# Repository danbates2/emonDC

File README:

emonDC
Project status: in production. expected release May 2018.

Measurement of direct current (DC).
This is a project description but also a collection of ideas and findings. All thoughts welcome.
The diversity of approaches could be illustrated by these two websites:
https://www.coolcomponents.co.uk/attopilot-voltage-and-current-sense-breakout-180a.html
http://www.victronenergy.com/upload/documents/Datasheet-Battery-monitoring-EN.pdf
My approach won’t be the only way but you’ll get an idea as you read on. Hopefully it makes sense. I welcome any and all feedback and hope for this to be as complete a project in theory before I begin schematic and PCB designs. Hey, I might even be close to making a decision by now… Also, this isn’t intended to claim ownership of the idea, if anyone wants to pick up the pieces and go for it they’re welcome.

emonDC Project
This unit will be a dual  shunt-monitoring device with wireless Tx capabilities. The device will be powered from the DC voltage source it is measuring, or from batteries. Because of potential outdoor applications the form will make possible the use of Waterproof I.P. rated boxes. A metal case matching emonTX style needs looking at also. The unit design will aim primarily at domestic DC applications, for example, solar photovoltaic and wind generation systems with either grid-tie inverters or battery systems.
Safety needs consideration in different ways. Firstly, short circuit protection needs to exist at different levels of the hardware design to avoid inadvertent damage to the unit, by mal-assembly on part of the manufacturer (PCB) or user (installation). This can be achieved with adding particular components, such as fuses and backup series resistors, in the event of a short. The layout of the components will factor in safety also.
Secondly, protection of connected devices and users from floating ground voltages in certain applications. This can be achieved with a bright yellow warning label stating ‘disconnect DC system before attaching USB/FTDI’ or ‘check for common ground between this unit and devices to be connected before making connection’ or something similar, pending advice.
Hall-effect DC monitoring ICs are simple and provide a degree of electrical isolation, however, they are inflexible and costly. Shunt monitoring provides much greater flexibility, accuracy and cost-effectiveness.

1. The range of requirements in DC monitoring applications require a flexible approach because of…
a. Unidirectional and bidirectional requirements.
b. Amperage Ranges and associated cable cross sectional areas (CSA). For example, household 100A cables are 25mm2 or 16mm2, whereas wire for headers and breadboard carrying up to about 5A are about 0.9mm2. The target measurement range has significant physical design implications. 
c. Different cable/wire CSAs require terminations suitable to their size and application (screw terminals, bolted bus bars, soldered connections, etc.) there is no single solution.
d. Whole battery systems can be monitored with one shunt or individual cells of the system can require a multi-cell monitoring unit.
e. There are also high humidity, marine and automotive applications.

2. If we consider cable sizes and the range of amperages in terms of a suitable termination, the issues make it difficult to see any one PCB realistically and cost-effectively meeting all requirements.
This possibly leads to the solution of designing several different systems according to the requirements. First suggestions might look like:
emonDC50 – Bidirectional DC monitor with integrated yet replaceable / bypassable shunt, accepting up to 6mm2 cable up to 50A, but with customizable sensitivity down for micro amps.
emonDC500 – Unidirectional shunt monitor with external shunt rated up to 500A.
emonDC500duo – Two unidirectional shunt monitors in parallel for measuring two external shunts rated up to 500A, for battery/generator applications.

3. Another option might be to have a two-part system where Tx functions are separated from shunt monitoring functions in two separate PCBs, connected via RJ11 or ribbon cable. This could lend itself to multi-source monitoring effectively. Several different model of the DC monitoring PCB could be developed for a range of applications. Also, the standalone Tx PCB may lend itself to other emon projects in the future.

4. Given the nature of solar, wind and various DC applications there a requirement for a protected, regulated supply. Protected from over voltage. Regulated, smoothed output for powering the shunt monitor, Arduino and RF chip.

5. Failsafe monitoring... Fuses between the shunt and monitor to protect from short circuit conditions.

6. High-side vs. low-side sensing… This shunt monitor needs to be capable of handling both applications, which means using a shunt monitor IC capable of high-side measurement. The device should ideally handle a large common-mode voltage, say up to 80V, and protection be in place for voltage over the common-mode voltage limit of the chip.

Project Aims
Follow on from previous research.
Create as flexible as possible unit. Aiming primarily at domestic solar and wind applications.
Compare hall-effect type to shunt monitor type DC measuring approaches, particularly in relation to safety, accuracy and flexibility.
Integrate wireless Tx function using RFM69CW.
Explore potential for AC monitoring applications.
To ascertain for certain the viability or necessity of a two part system. Such as Part A: Tx PCB and Part B: DC monitoring shield.
Investigate a calibration routine storing data in EEPROM.
Look at case design.
Look at the energy efficiency of different manufacturing approaches.
Make a unit!

Unit Features
Focusing on the proposed emonDC50…
Single PCB approach.
emonTx functions including RF and Arduino.
DC monitoring chip capable of bidirectional monitoring for 24V wind and solar systems.. common mode voltage capability of 40V ish..
Screw terminal or soldered connections accepting 6mm2.
Replaceable shunt or perhaps a jumper to disconnect the onboard shunt, then through holes for connecting a specified resistor.

Questions…
What’s the relationship to different amperages, cables sizes and suitable cable terminations at the device?
Would a particular amperage range require soldered connection? Do specific applications require soldered connections?
Could the PCB safely handle the required amps? What’s the current carrying capacity of header pins and PCB track?
Can PCB track be used as the shunt?
How does heat dissipate through the PCB and how does this effect the value being monitored? Is a temp sensor required for factoring in temperature drift?

Notes:
In wind and solar applications cable is often sized according to the length of the run from the generator to the batteries, in this instance the installer will have to adapt for the relevant termination.

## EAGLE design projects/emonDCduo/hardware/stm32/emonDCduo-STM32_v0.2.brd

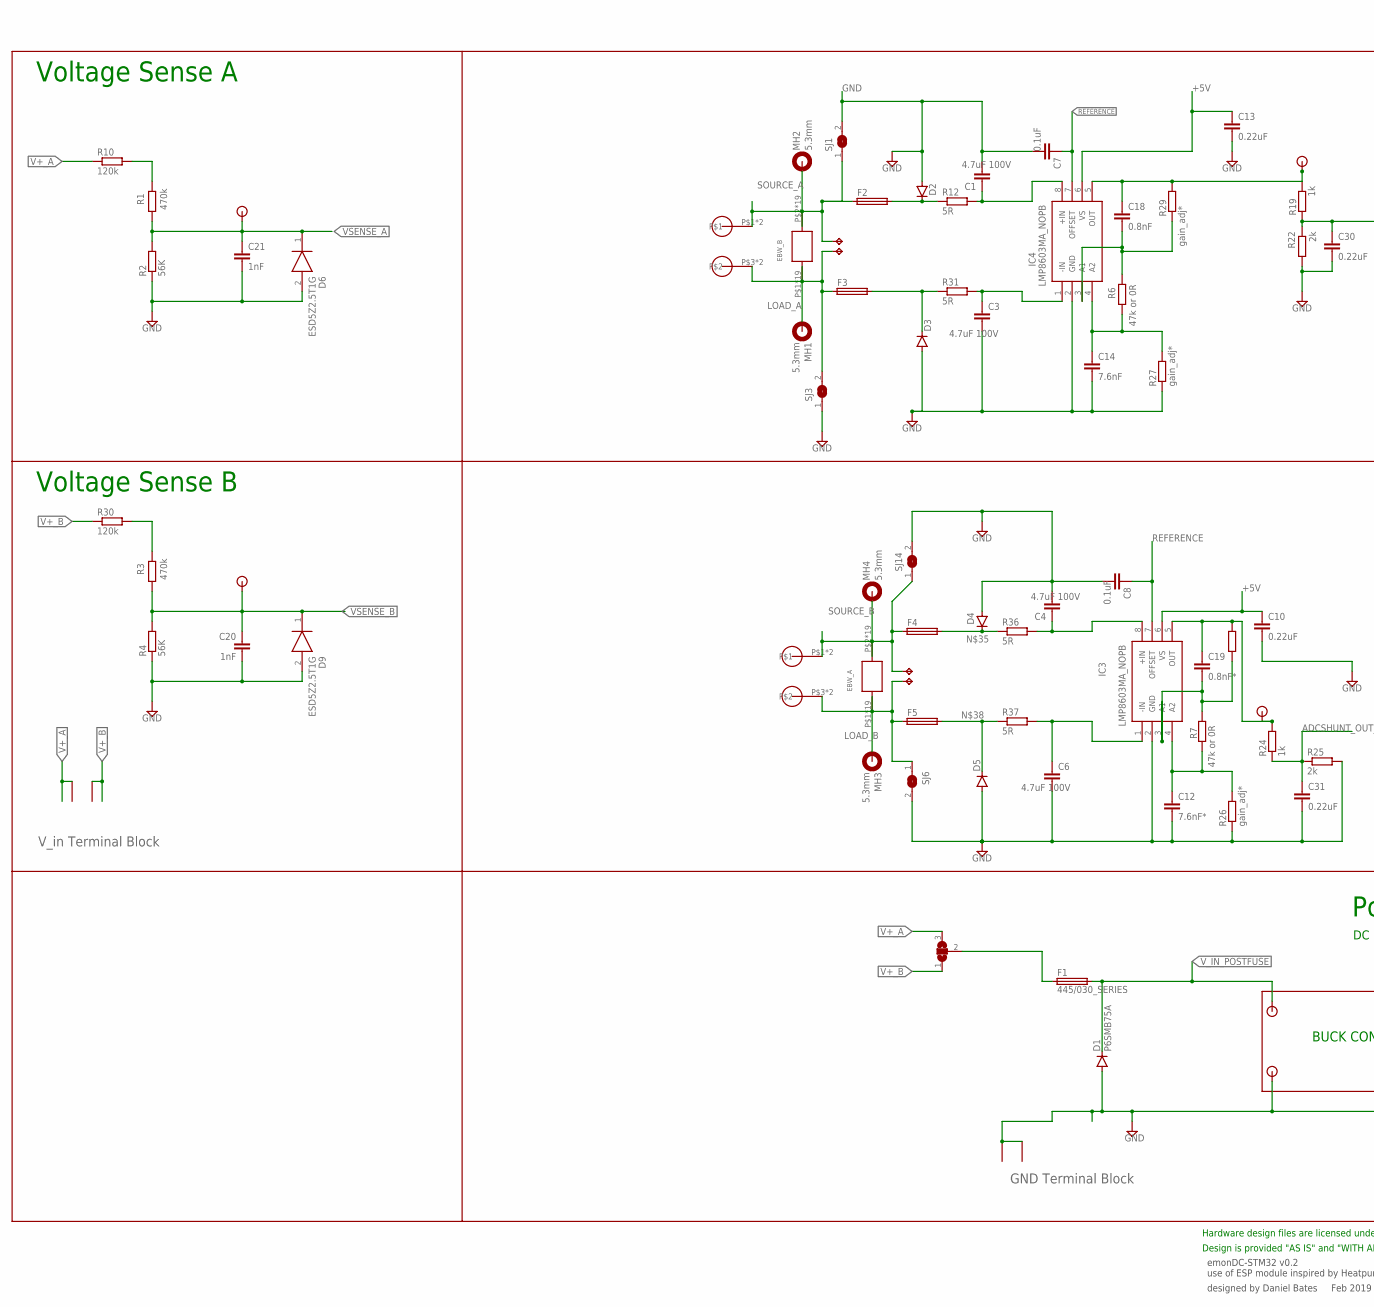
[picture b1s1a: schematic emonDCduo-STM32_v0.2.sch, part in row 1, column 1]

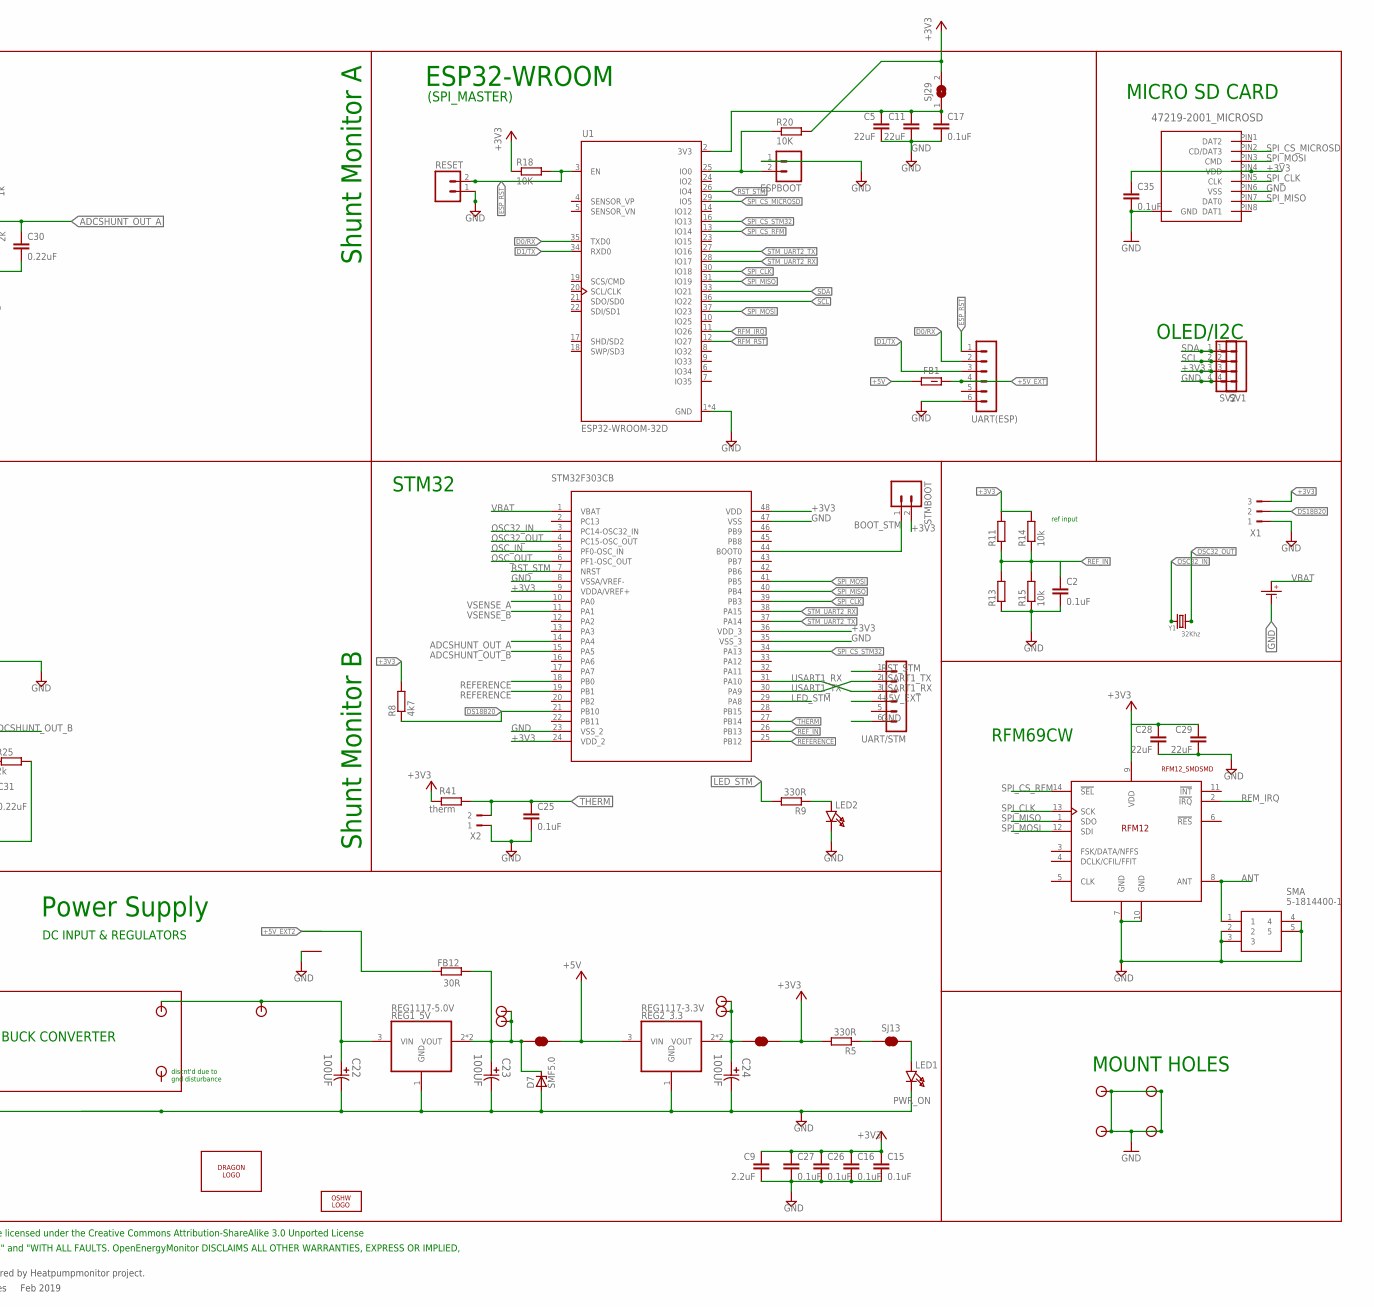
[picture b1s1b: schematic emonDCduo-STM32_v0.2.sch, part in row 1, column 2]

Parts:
3V3, 5V: JUMPER-SMT_2_NC_TRACE_NO-SILK; SMT-JUMPER_2_NC_TRACE_NO-SILK
C1, C3, C4, C6: 4.7uF 100V; C1206; MPN C1608X7S2A104K080AB
C2, C15, C16, C17, C25, C26, C27, C35: 0.1uF; C0603
C5, C11, C28, C29: 22uF; C0805
C7, C8: 0.1uF; C0603; MPN C1608X7S2A104K080AB
C9: 2.2uF; C0805
C10, C13, C30, C31: 0.22uF; C0603; MPN C1608X7S2A104K080AB
C12: 7.6nF*; C0603
C14: 7.6nF; C0603; MPN C1608X7S2A104K080AB
C18: 0.8nF; C0603; MPN C1608X7S2A104K080AB
C19: 0.8nF*; C0603; MPN C1608X7S2A104K080AB
C20, C21: 1nF; C0603; MPN C1608X7S2A104K080AB
C22, C23, C24: 100UF; CAPAE530X610N
CR1220: CR1220SMD; MPN Harwin S8411-45R
D1: P6SMB75A; DO214AA
D2, D3, D4, D5: P6SMB75A; SMB
D6, D9: ESD5Z2.5T1G; SODFL1608X70N
D7: SMF5.0; SOD123F
EBW_A: EBW_SERIES_15.2MM
EBW_B: EBW_SERIES_15.2MM
ESPBOOT: M02PTH; 1X02
F1: 445/030_SERIES; 445/030_SERIES_LITTELFUSE
F2, F3, F4, F5: TR5
FB1: FBCHIP-0603(1608-METRIC); BEADC1608X95N
FB12: 30R; R0603
IC3, IC4: LMP8603MA_NOPB; SOIC127P600X175-8N
LED1, LED2: PWR_ON; CHIPLED_1206
LOGO1: OSHW_LOGO_6MILX0200-NT; OSHW_6X200_NOTEXT
MH1, MH2, MH3, MH4: 5.3mm; 5,3//11-PAD
MICRO_SD: 47219-2001_MICROSD
MOUNT_10.16_A, MOUNT_10.16_B: MOLEX_39970-003; 2/10,16
R1, R3: 470k; 0207/2V; MPN MCMF006FF1004A50
R2, R4: 56K; R0603; MPN MCMF006FF7502A50
R5, R9: 330R; R0603
R6, R7: 47k or 0R; R0603
R8: 4k7; R0603
R10, R30: 120k; R0603; MPN MCMF006FF1004A50
R11, R13: R-EU_0207/2V; 0207/2V
R12, R31, R36, R37: 5R; R0603; MPN MCMF006FF1004A50
R14, R15: 10k; R0603
R18, R20: 10K; R0603
R19, R24: 1k; R0603; MPN MCMF006FF1004A50
R22, R25: 2k; R0603; MPN MCMF006FF1004A50
R26, R27, R28, R29: gain_adj*; R0603; MPN MCMF006FF1004A50
R41: therm; R0603
REG1_5V: REG1117-5.0V; SOT223; MPN REG1117-5.0
REG2_3.3: REG1117-3.3V; SOT223; MPN REG1117-3.3
RESET: M02PTH; 1X02
SJ1, SJ3, SJ6, SJ14, SJ29: SJ
SJ13: JUMPER-SMT_2_NC_TRACE_NO-SILK; SMT-JUMPER_2_NC_TRACE_NO-SILK
SJ15: SJ2W; SJ_2
SMA: 5-1814400-1; 518144001
STM32F303CB: STM32F303CB_STM32F302_303C2; STM32F303CB_LQFP48-7X7MM; MANUFACTURER_PART_NUMBER STM32F303CB
STMBOOT: M02PTH; 1X02
SV1, SV2: MA04-1; MPN 2212S-04SG-85
TP8, TP9, TP10, TP11: TPPAD1-13Y; P1-13Y
U1: ESP32-WROOM-32D; MODULE_ESP32-WROOM-32D
U$1, U$4, U$5, U$6, U$7, U$8, U$9, U$18, U$19: TP0.8MM; TP0.8
U$2, U$3, U$10, U$11: 2212S-02SG-85; TP0.8_X2
U$14: RFM12_SMDSMD; RFM12
U$15, U$16, U$17: 7.62MM_TERMINAL_BLOCK; 7.62MM
U$22, U$23, U$24, U$25: TP3.5MM; TP3.5
U$26: DRAGON; DRAGON_LOGO
UART(ESP): UART/ESP; MA06-1
UART/STM: UART/STM; MA06-1
X1: 180-3
X2: 180-2
Y1: 32Khz; CRYSTAL_8X3.8

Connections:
3.3V_: 3V3.1, C24.1, REG2_3.3.2 (VOUT), REG2_3.3.4 (VOUT), U$8.P$1, U$19.P$1
5V_: 5V.1, C23.1, D7.C, FB12.1, REG1_5V.2 (VOUT), REG1_5V.4 (VOUT), U$7.P$1, U$18.P$1
6.5V: C22.1, REG1_5V.3 (VIN), U$9.P$1, U$10.P$1, U$10.P$2
+3V3: 3V3.2, C9.1, C15.1, C16.1, C26.1, C27.1, C28.1, C29.1, C35.1, MICRO_SD.PIN4 (VDD), R5.2, R8.2, R11.2, R14.2, R18.1, R20.2, R41.2, SJ29.2, STM32F303CB.9 (VDDA/VREF+), STM32F303CB.24 (VDD_2), STM32F303CB.36 (VDD_3), STM32F303CB.48 (VDD), STMBOOT.2, SV1.3, SV2.3, U$14.9 (VDD), X1.3
+3V3_ESP: C5.1, C11.1, C17.1, SJ29.1, U1.2 (3V3)
+5V: 5V.2, C10.1, C13.1, FB1.1, IC3.6 (VS), IC4.6 (VS), REG2_3.3.3 (VIN)
+5V_EXT: FB1.2, UART(ESP).4, UART/STM.4
+5V_EXT2: FB12.2, U$17.P$1
ADCSHUNT_OUT_A: C30.1, R19.1, R22.1, STM32F303CB.14 (PA4)
ADCSHUNT_OUT_A_: C18.1, IC4.5 (OUT), R19.2, R29.2, U$6.P$1
ADCSHUNT_OUT_B: C31.1, R24.1, R25.1, STM32F303CB.15 (PA5)
ADCSHUNT_OUT_B_: C19.1, IC3.5 (OUT), R24.2, R28.2, U$5.P$1
ANT: SMA.1, U$14.8 (ANT)
BOOT_STM: STM32F303CB.44 (BOOT0), STMBOOT.1
D0/RX: U1.35 (TXD0), UART(ESP).2
D1/TX: U1.34 (RXD0), UART(ESP).3
DS18B20: R8.1, STM32F303CB.21 (PB10), X1.2
ESP_RST: R18.2, RESET.2, U1.3 (EN), UART(ESP).1
GND: C1.2, C2.2, C3.2, C4.2, C5.2, C6.2, C7.2, C8.2, C9.2, C10.2, C11.2, C12.2, C13.2, C14.2, C15.2, C16.2, C17.2, C20.2, C21.2, C22.2, C23.2, C24.2, C25.2, C26.2, C27.2, C28.2, C29.2, C30.2, C31.2, C35.2, CR1220.P- (P$-), D1.A, D2.A, D3.A, D4.A, D5.A, D6.2 (A), D7.A, D9.2 (A), ESPBOOT.1, IC3.2 (GND), IC4.2 (GND), LED1.C, LED2.C, MICRO_SD.P$1 (GND), MICRO_SD.P$2 (GND), MICRO_SD.P$3 (GND), MICRO_SD.P$4 (GND), MICRO_SD.PIN6 (VSS), R2.1, R4.1, R13.1, R15.1, R22.2, R25.2, R26.1, R27.1, REG1_5V.1 (GND), REG2_3.3.1 (GND), RESET.1, SJ1.2, SJ3.1, SJ6.2, SJ14.2, SMA.2, SMA.3, SMA.4, SMA.5, STM32F303CB.8 (VSSA/VREF-), STM32F303CB.23 (VSS_2), STM32F303CB.35 (VSS_3), STM32F303CB.47 (VSS), SV1.4, SV2.4, U1.1 (GND), U1.15 (GND), U1.38 (GND), U1.39 (GND), U$3.P$1, U$3.P$2, U$14.7 (GND), U$14.10 (GND), U$16.P$1, U$16.P$2, U$17.P$2, U$22.P$1, U$23.P$1, U$24.P$1, U$25.P$1, UART(ESP).6, UART/STM.6, X1.1, X2.1
LED_STM: R9.2, STM32F303CB.29 (PA8)
LOAD_A: EBW_B.P$1, EBW_B.P$3, EBW_B.P$4, EBW_B.P$5, EBW_B.P$6, EBW_B.P$7, EBW_B.P$8, EBW_B.P$9, EBW_B.P$10, EBW_B.P$11, EBW_B.P$12, EBW_B.P$13, EBW_B.P$14, EBW_B.P$15, EBW_B.P$16, EBW_B.P$17, EBW_B.P$33, EBW_B.P$34, EBW_B.P$35, F3.1, MH1.B5,5, MOUNT_10.16_A.P$3, MOUNT_10.16_A.P$4, SJ3.2, TP10.TP
LOAD_B: EBW_A.P$1, EBW_A.P$3, EBW_A.P$4, EBW_A.P$5, EBW_A.P$6, EBW_A.P$7, EBW_A.P$8, EBW_A.P$9, EBW_A.P$10, EBW_A.P$11, EBW_A.P$12, EBW_A.P$13, EBW_A.P$14, EBW_A.P$15, EBW_A.P$16, EBW_A.P$17, EBW_A.P$33, EBW_A.P$34, EBW_A.P$35, F5.1, MH3.B5,5, MOUNT_10.16_B.P$3, MOUNT_10.16_B.P$4, SJ6.1, TP8.TP
LOAD_B_T: C6.1, IC3.1 (-IN), R37.2
LOAD_T_A: C3.1, IC4.1 (-IN), R31.2
unnamed: C14.1, IC4.4 (A2), R6.2, R27.2
unnamed: C18.2, IC4.3 (A1), R6.1, R29.1
unnamed: R5.1, SJ13.1
unnamed: LED1.A, SJ13.2
unnamed: F1.P$1 (1), F1.P$2 (1), SJ15.2
unnamed: R3.1, R30.2
unnamed: R1.1, R10.2
unnamed: C19.2, IC3.3 (A1), R7.1, R28.1
unnamed: C12.1, IC3.4 (A2), R7.2, R26.2
unnamed: ESPBOOT.2, R20.1, U1.25 (IO0)
unnamed: LED2.A, R9.1
unnamed: D2.C, F2.2, R12.1
unnamed: D3.C, F3.2, R31.1
unnamed: D4.C, F4.2, R36.1
unnamed: D5.C, F5.2, R37.1
OSC32_IN: STM32F303CB.3 (PC14-OSC32_IN), Y1.P$1 (1)
OSC32_OUT: STM32F303CB.4 (PC15-OSC_OUT), Y1.P$4 (2)
OSC_IN: STM32F303CB.5 (PF0-OSC_IN)
OSC_OUT: STM32F303CB.6 (PF1-OSC_OUT)
REFERENCE: C7.1, C8.1, IC3.7 (OFFSET), IC4.7 (OFFSET), STM32F303CB.18 (PB0), STM32F303CB.19 (PB1), STM32F303CB.25 (PB12)
REF_IN: C2.1, R11.1, R13.2, R14.1, R15.2, STM32F303CB.26 (PB13)
RFM_IRQ: U1.11 (IO26), U$14.2 (!IRQ)
RFM_RST: U1.12 (IO27)
RST_STM: STM32F303CB.7 (NRST), U1.26 (IO4), UART/STM.1
SCL: SV1.2, SV2.2, U1.36 (IO22)
SDA: SV1.1, SV2.1, U1.33 (IO21)
SOURCE_A: EBW_B.P$2, EBW_B.P$18, EBW_B.P$19, EBW_B.P$20, EBW_B.P$21, EBW_B.P$22, EBW_B.P$23, EBW_B.P$24, EBW_B.P$25, EBW_B.P$26, EBW_B.P$27, EBW_B.P$28, EBW_B.P$29, EBW_B.P$30, EBW_B.P$31, EBW_B.P$32, EBW_B.P$36, EBW_B.P$37, EBW_B.P$38, F2.1, MH2.B5,5, MOUNT_10.16_A.P$1, MOUNT_10.16_A.P$2, SJ1.1, TP11.TP
SOURCE_B: EBW_A.P$2, EBW_A.P$18, EBW_A.P$19, EBW_A.P$20, EBW_A.P$21, EBW_A.P$22, EBW_A.P$23, EBW_A.P$24, EBW_A.P$25, EBW_A.P$26, EBW_A.P$27, EBW_A.P$28, EBW_A.P$29, EBW_A.P$30, EBW_A.P$31, EBW_A.P$32, EBW_A.P$36, EBW_A.P$37, EBW_A.P$38, F4.1, MH4.B5,5, MOUNT_10.16_B.P$1, MOUNT_10.16_B.P$2, SJ14.1, TP9.TP
SOURCE_B_T: C4.1, IC3.8 (+IN), R36.2
SOURCE_T_A: C1.1, IC4.8 (+IN), R12.2
SPI_CLK: MICRO_SD.PIN5 (CLK), STM32F303CB.39 (PB3), U1.30 (IO18), U$14.13 (SCK)
SPI_CS_MICROSD: MICRO_SD.PIN2 (CD/DAT3), U1.29 (IO5)
SPI_CS_RFM: U1.13 (IO14), U$14.14 (!SEL)
SPI_CS_STM32: STM32F303CB.34 (PA13), U1.16 (IO13)
SPI_MISO: MICRO_SD.PIN7 (DAT0), STM32F303CB.40 (PB4), U1.31 (IO19), U$14.1 (SDO)
SPI_MOSI: MICRO_SD.PIN3 (CMD), STM32F303CB.41 (PB5), U1.37 (IO23), U$14.12 (SDI)
STM_UART2_RX: STM32F303CB.38 (PA15), U1.28 (IO17)
STM_UART2_TX: STM32F303CB.37 (PA14), U1.27 (IO16)
THERM: C25.1, R41.1, STM32F303CB.27 (PB14), X2.2
USART1_RX: STM32F303CB.31 (PA10), UART/STM.3
USART1_TX: STM32F303CB.30 (PA9), UART/STM.2
V+_A: R10.1, SJ15.3, U$15.P$2
V+_B: R30.1, SJ15.1, U$15.P$1
VBAT: CR1220.P+ (P$+), STM32F303CB.1 (VBAT)
VSENSE_A: C21.1, D6.1 (K), R1.2, R2.2, STM32F303CB.10 (PA0), U$1.P$1
VSENSE_B: C20.1, D9.1 (K), R3.2, R4.2, STM32F303CB.11 (PA1), U$4.P$1
V_IN_POSTFUSE: D1.C, F1.P$3 (2), F1.P$4 (2), U$2.P$1, U$2.P$2

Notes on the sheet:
emonDC-STM32 v0.2 use of ESP module inspired by Heatpumpmonitor project.
designed by Daniel Bates Feb 2019
Power Supply
Design is provided "AS IS" and "WITH ALL FAULTS. OpenEnergyMonitor DISCLAIMS ALL OTHER WARRANTIES, EXPRESS OR IMPLIED,
Hardware design files are licensed under the Creative Commons Attribution-ShareAlike 3.0 Unported License
DC INPUT & REGULATORS
Shunt Monitor B
Shunt Monitor A
ESP32-WROOM
MICRO SD CARD
STM32
MOUNT HOLES
OLED/I2C
RFM69CW
Voltage Sense A
Voltage Sense B
V_in Terminal Block
GND Terminal Block
(SPI_MASTER)
BUCK CONVERTER
discnt'd due to gnd disturbance
ref input

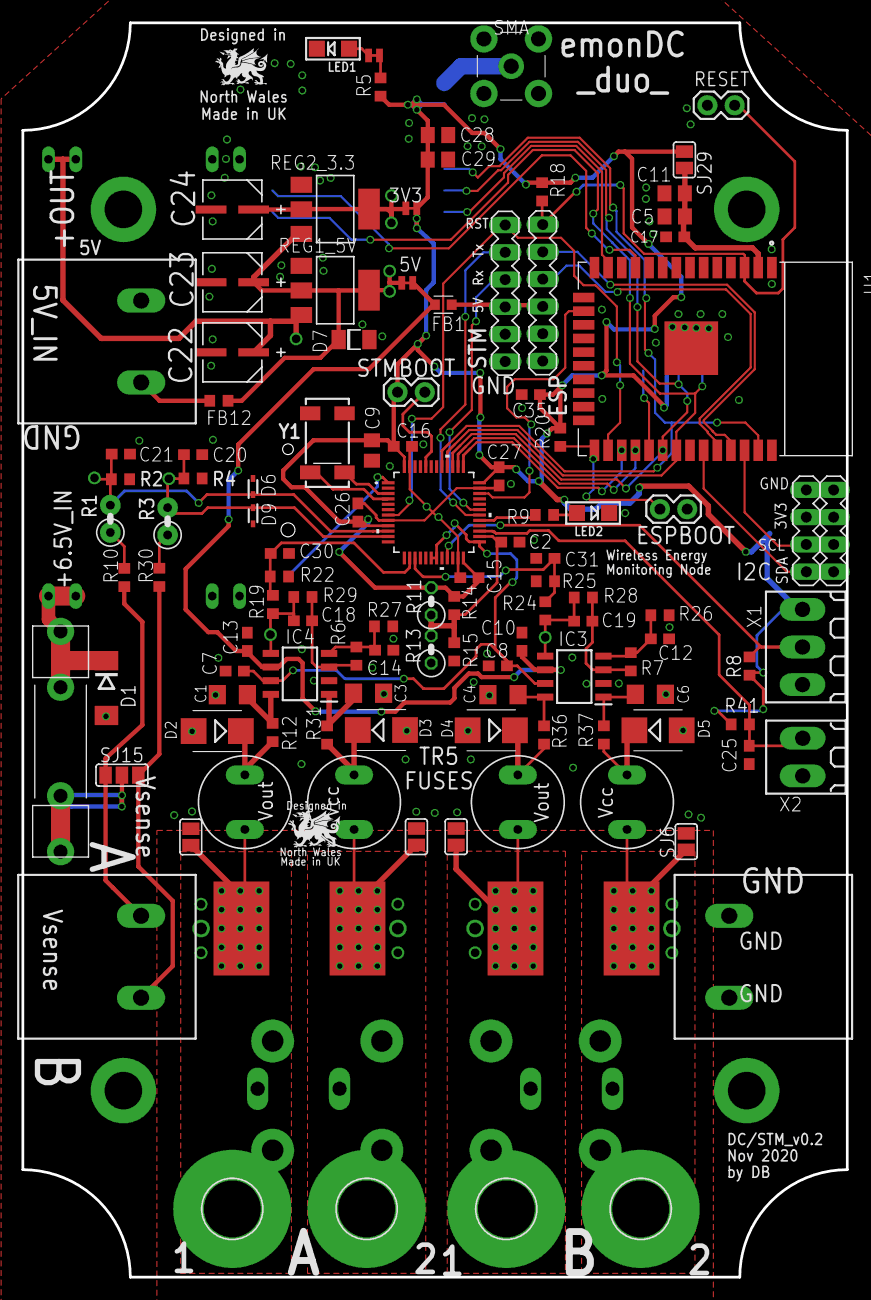
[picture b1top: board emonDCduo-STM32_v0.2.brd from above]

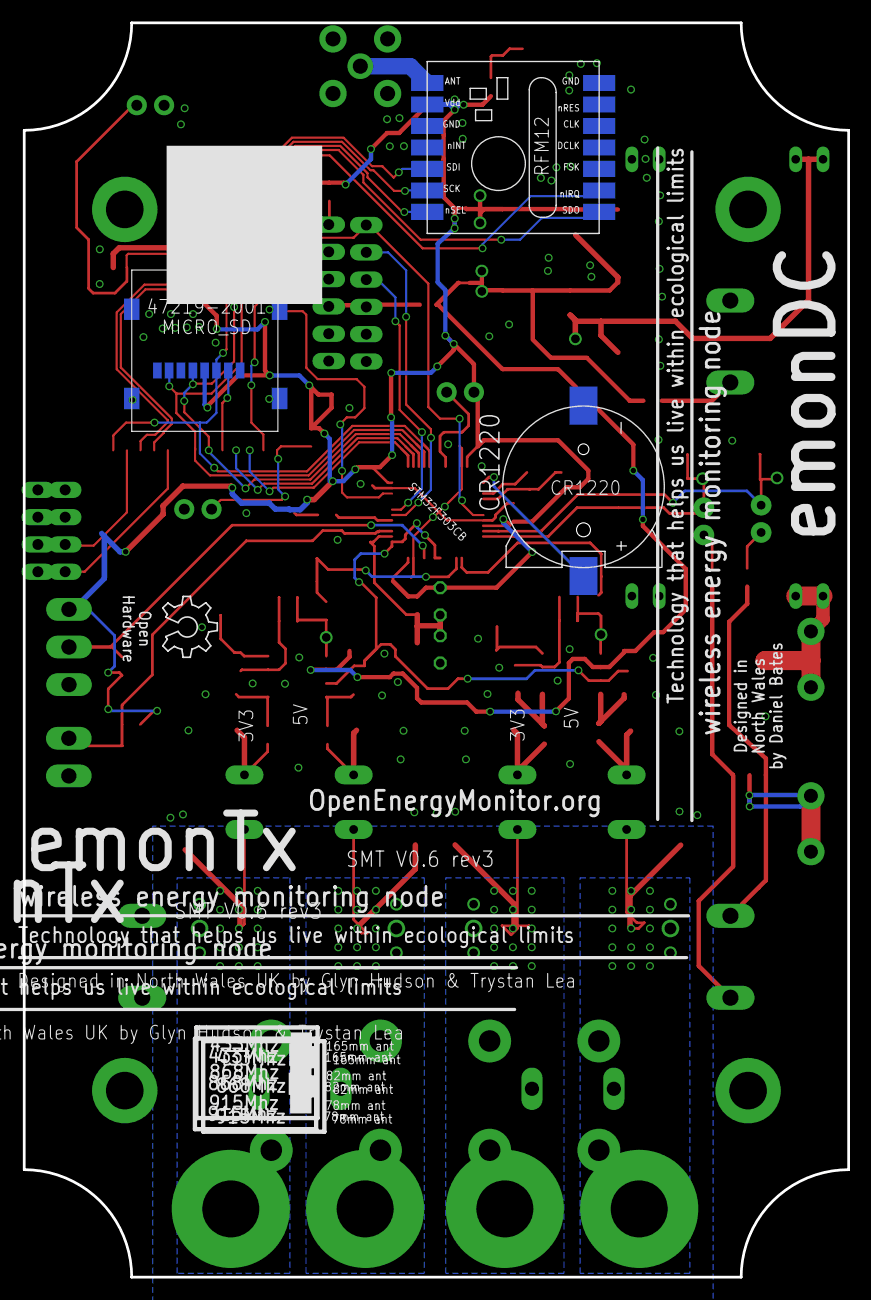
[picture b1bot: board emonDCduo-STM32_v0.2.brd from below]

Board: 2 copper layers, 76.7 x 116.7 mm, 142 parts (4 on the bottom side), 68 nets.

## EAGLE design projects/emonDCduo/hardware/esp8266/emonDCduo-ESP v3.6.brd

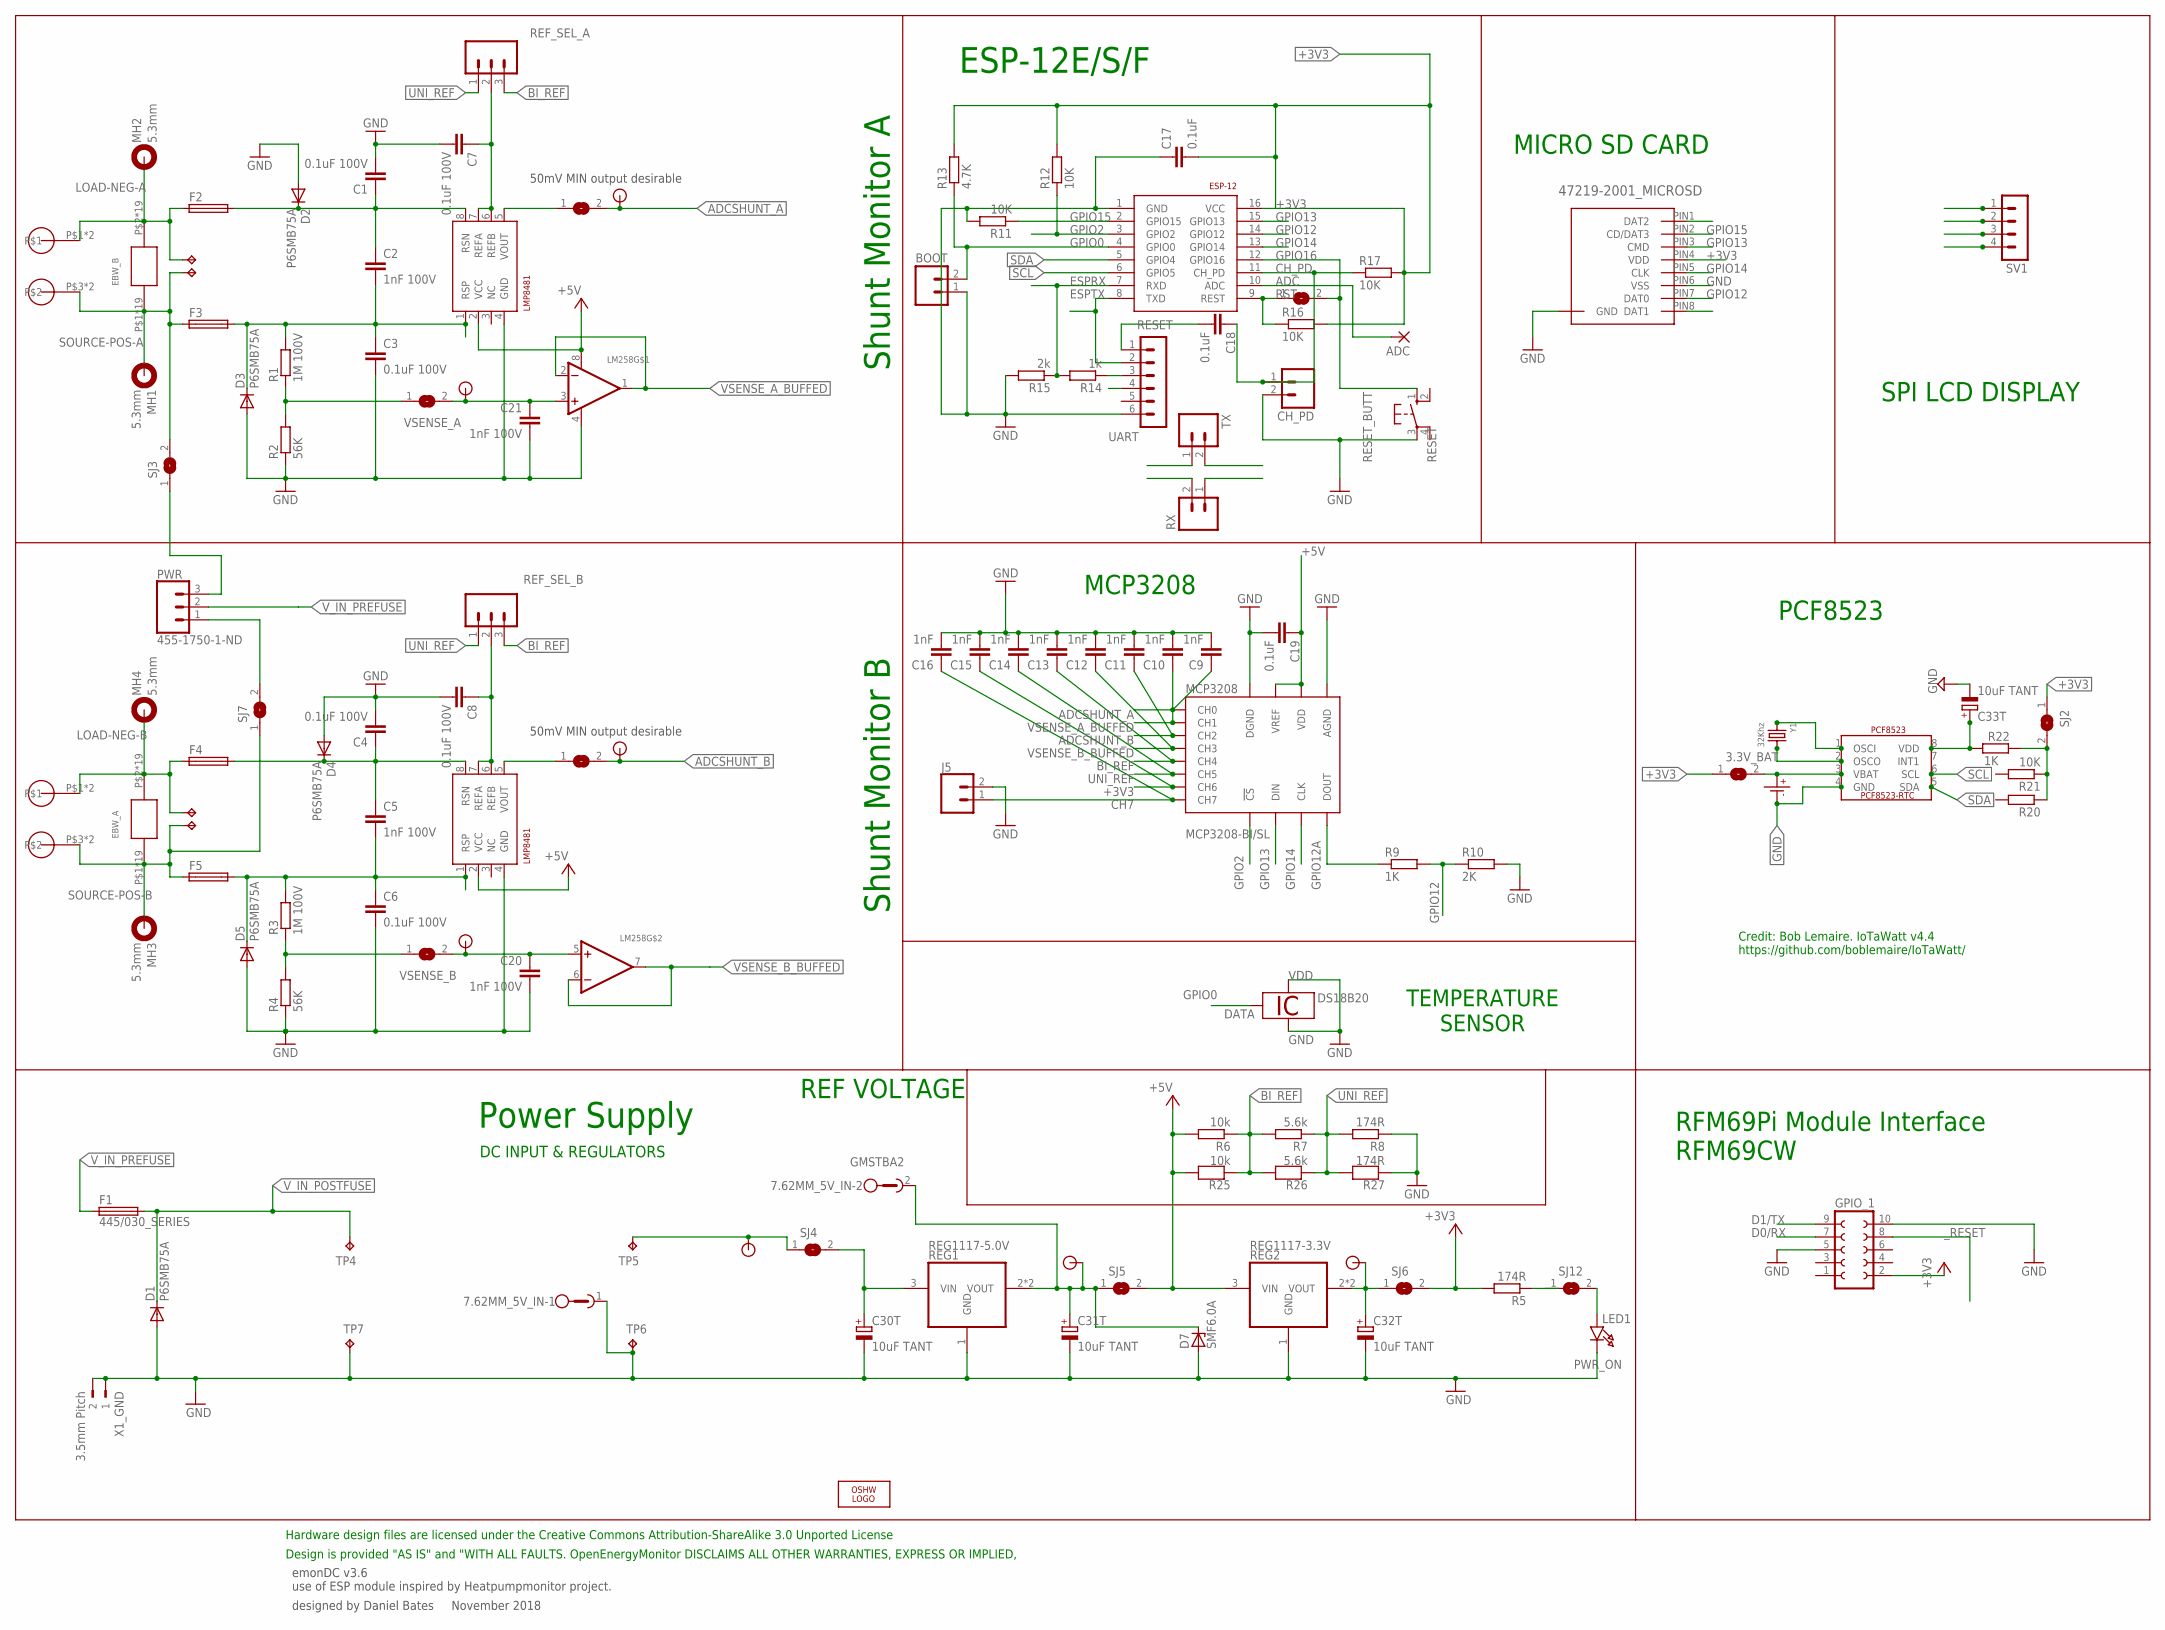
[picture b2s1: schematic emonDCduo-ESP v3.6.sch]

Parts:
3.3V_BAT: SOLDERJUMPERCLOSED; SOLDERJUMPER_CLOSEDWIRE
7.62MM_5V_IN: GMSTBA2
ADC: 2,15/1,0
BOOT: M02PTH; 1X02
C1, C3, C4, C6, C7, C8: 0.1uF 100V; C0603; MPN C1608X7S2A104K080AB
C2, C5, C20, C21: 1nF 100V; C0603; MPN C1608X7S2A104K080AB
C9, C10, C11, C12, C13, C14, C15, C16: 1nF; C0603
C17, C18, C19: 0.1uF; C0603
C30T, C31T, C32T, C33T: 10uF TANT; C0603POL
CH_PD: M02PTH; 1X02
CR1220: CR1220SMD; MPN Harwin S8411-45R
D1, D2, D3, D4, D5: P6SMB75A; DO214AA
D7: SMF6.0A; SOD123F
EBW_A: EBW_SERIES_15.2MM
EBW_B: EBW_SERIES_15.2MM
ESP-12: ESP8266_ESP-12; ESP8266-ESP12
F1: 445/030_SERIES; 445/030_SERIES_LITTELFUSE
F2, F3, F4, F5: TR5
GPIO_1: FE05-2_RFM69PI_OUTLINERFM69PI; FE05-2_RFM69PI_OULTINE
IC1: DS18B20; TO92-
J5: CONN_02; 1X02
LED1: PWR_ON; CHIPLED_1206
LM258: LM358; SOIC8_150MIL
LOGO1: OSHW_LOGO_6MILX0200-NT; OSHW_6X200_NOTEXT
MCP3208: MCP3208-BI/SL; SOIC16
MH1, MH2, MH3, MH4: 5.3mm; 5,3//11-PAD
MICRO_SD: 47219-2001_MICROSD
MOUNT_10.16_A, MOUNT_10.16_B: MOLEX_39970-003; 2/10,16
PCF8523: PCF8523_RTC; SOIC_8
PWR: 455-1750-1-ND; 1X03
R1, R3: 1M 100V; 0207/2V; MPN MCWR06X1003FTL
R2, R4: 56K; 0207/2V; MPN MCWR06X5901FTL
R5: 174R; R0603
R6: 10k; 0207/10
R7: 5.6k; 0207/10
R8: 174R; 0207/10
R9: 1K; R0603; MPN MCWR06X5901FTL
R10: 2K; R0603; MPN MCWR06X5901FTL
R11, R12, R16, R17, R20, R21: 10K; R0603
R13: 4.7K; R0603
R14: 1k; R0603
R15: 2k; R0603
R22: 1K; R0603
R25: 10k; 0603
R26: 5.6k; 0603
R27: 174R; 0603
REF_SEL_A: 455-1750-1-ND; 1X03; MPN 2212S-02SG-85
REF_SEL_B: 455-1750-1-ND; 1X03; MPN 2212S-02SG-85
REG1: REG1117-5.0V; SOT223; MPN REG1117-5.0
REG2: REG1117-3.3V; SOT223; MPN REG1117-3.3
RESET: RESET_BUTT; B3F-10XX
RX: M02PTH; 1X02
SHUNTMON-A: LMP8481; S-PDSO-G08; MPN LMP8481MME-S/NOPB
SHUNTMON-B: LMP8481; S-PDSO-G08; MPN LMP8481MME-H/NOPB
SJ1, SJ2, SJ4, SJ5, SJ6, SJ8, SJ9, SJ10, SJ11: SOLDERJUMPERCLOSED; SOLDERJUMPER_CLOSEDWIRE
SJ3, SJ7, SJ12: SJ
SV1: MA04-1
TP4, TP5, TP6, TP7, TP8, TP9, TP10, TP11: TPPAD1-13Y; P1-13Y
TX: M02PTH; 1X02
U$1, U$4, U$5, U$6, U$7, U$8, U$9: TP0.8MM; TP0.8
UART: UART; MA06-1
X1_GND: 3.5mm Pitch; 180-2
Y1: 32Khz; CRYSTAL_8X3.8

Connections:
3.3V_PRE: C32T.1 (+), REG2.2 (VOUT), REG2.4 (VOUT), SJ6.1, U$8.P$1
5V_PRE: 7.62MM_5V_IN.2, C31T.1 (+), D7.C, REG1.2 (VOUT), REG1.4 (VOUT), SJ5.1, U$7.P$1
6.5V: C30T.1 (+), REG1.3 (VIN), SJ4.2
+3V3: 3.3V_BAT.1, C15.1, C17.2, ESP-12.16 (VCC), GPIO_1.2, MCP3208.7 (CH6), MICRO_SD.PIN4 (VDD), R5.2, R12.2, R13.2, R16.2, R17.2, SJ2.1, SJ6.2, SV1.3
+5V: C19.1, LM258.8 (V+), MCP3208.15 (VREF), MCP3208.16 (VDD), R6.2, R25.2, REG2.3 (VIN), SHUNTMON-A.2 (VCC), SHUNTMON-B.2 (VCC), SJ5.2, UART.4
ADC: ADC.1, ESP-12.10 (ADC)
ADCSHUNT_A: C9.1, MCP3208.1 (CH0), SJ11.2, U$6.P$1
ADCSHUNT_B: C11.1, MCP3208.3 (CH2), SJ10.2, U$5.P$1
BI_REF: C13.1, MCP3208.5 (CH4), R6.1, R7.2, R25.1, R26.2, REF_SEL_A.3, REF_SEL_B.3
CH7: C16.1, J5.1, MCP3208.8 (CH7)
CH_PD: C18.1, CH_PD.1, ESP-12.11 (CH_PD), R17.1
D0/RX: GPIO_1.7, TX.2
D1/TX: GPIO_1.9, RX.1
ESPRX: ESP-12.7 (RXD), R14.2, R15.1, RX.2
ESPTX: ESP-12.8 (TXD), TX.1, UART.2
GND: 7.62MM_5V_IN.1, BOOT.1, C1.2, C3.2, C4.2, C6.2, C7.2, C8.2, C9.2, C10.2, C11.2, C12.2, C13.2, C14.2, C15.2, C16.2, C17.1, C19.2, C20.2, C21.2, C30T.2 (-), C31T.2 (-), C32T.2 (-), C33T.2 (-), CH_PD.2, CR1220.P- (P$-), D1.A, D2.A, D3.A, D4.A, D5.A, D7.A, ESP-12.1 (GND), GPIO_1.5, GPIO_1.10, IC1.1 (GND), IC1.3 (VDD), J5.2, LED1.C, LM258.4 (V-), MCP3208.9 (DGND), MCP3208.14 (AGND), MICRO_SD.P$1 (GND), MICRO_SD.P$2 (GND), MICRO_SD.P$3 (GND), MICRO_SD.P$4 (GND), MICRO_SD.PIN6 (VSS), PCF8523.4 (GND), R2.1, R4.1, R8.1, R10.2, R11.2, R15.2, R27.1, REG1.1 (GND), REG2.1 (GND), RESET.3, SHUNTMON-A.4 (GND), SHUNTMON-B.4 (GND), SV1.4, TP6.TP, TP7.TP, UART.6, X1_GND.1, X1_GND.2
GPIO0: BOOT.2, ESP-12.4 (GPIO0), IC1.2 (DATA), R13.1
GPIO2: ESP-12.3 (GPIO2), MCP3208.10 (!CS), R12.1
GPIO12: ESP-12.14 (GPIO12), MICRO_SD.PIN7 (DAT0), R9.2, R10.1
GPIO12A: MCP3208.12 (DOUT), R9.1
GPIO13: ESP-12.15 (GPIO13), MCP3208.11 (DIN), MICRO_SD.PIN3 (CMD)
GPIO14: ESP-12.13 (GPIO14), MCP3208.13 (CLK), MICRO_SD.PIN5 (CLK)
GPIO15: ESP-12.2 (GPIO15), MICRO_SD.PIN2 (CD/DAT3), R11.1
GPIO16: ESP-12.12 (GPIO16), RESET.1 (S), SJ1.2
LOAD-NEG-A: EBW_B.P$2, EBW_B.P$18, EBW_B.P$19, EBW_B.P$20, EBW_B.P$21, EBW_B.P$22, EBW_B.P$23, EBW_B.P$24, EBW_B.P$25, EBW_B.P$26, EBW_B.P$27, EBW_B.P$28, EBW_B.P$29, EBW_B.P$30, EBW_B.P$31, EBW_B.P$32, EBW_B.P$36, EBW_B.P$37, EBW_B.P$38, F2.1, MH2.B5,5, MOUNT_10.16_A.P$1, MOUNT_10.16_A.P$2, TP11.TP
LOAD-NEG-A_T: C1.1, C2.1, D2.C, F2.2, SHUNTMON-A.8 (RSN)
LOAD-NEG-B: EBW_A.P$2, EBW_A.P$18, EBW_A.P$19, EBW_A.P$20, EBW_A.P$21, EBW_A.P$22, EBW_A.P$23, EBW_A.P$24, EBW_A.P$25, EBW_A.P$26, EBW_A.P$27, EBW_A.P$28, EBW_A.P$29, EBW_A.P$30, EBW_A.P$31, EBW_A.P$32, EBW_A.P$36, EBW_A.P$37, EBW_A.P$38, F4.1, MH4.B5,5, MOUNT_10.16_B.P$1, MOUNT_10.16_B.P$2, TP9.TP
LOAD-NEG-B_T: C4.1, C5.1, D4.C, F4.2, SHUNTMON-B.8 (RSN)
unnamed: SJ4.1, TP5.TP, U$9.P$1
unnamed: PWR.3, SJ3.1
unnamed: PWR.1, SJ7.2
unnamed: R5.1, SJ12.1
unnamed: LED1.A, SJ12.2
unnamed: SHUNTMON-B.5 (VOUT), SJ10.1
unnamed: SHUNTMON-A.5 (VOUT), SJ11.1
unnamed: R14.1, UART.3
unnamed: PCF8523.2 (OSCO), Y1.P$4 (2)
unnamed: PCF8523.1 (OSCI), Y1.P$1 (1)
REF_A_INPUT: C7.1, REF_SEL_A.2, SHUNTMON-A.6 (REFB), SHUNTMON-A.7 (REFA)
REF_B_INPUT: C8.1, REF_SEL_B.2, SHUNTMON-B.6 (REFB), SHUNTMON-B.7 (REFA)
RESET: C18.2, UART.1
RST: ESP-12.9 (REST), R16.1, SJ1.1
SCL: ESP-12.6 (GPIO5), PCF8523.6 (SCL), SV1.2
SDA: ESP-12.5 (GPIO4), PCF8523.5 (SDA), SV1.1
SOURCE-POS-A: EBW_B.P$1, EBW_B.P$3, EBW_B.P$4, EBW_B.P$5, EBW_B.P$6, EBW_B.P$7, EBW_B.P$8, EBW_B.P$9, EBW_B.P$10, EBW_B.P$11, EBW_B.P$12, EBW_B.P$13, EBW_B.P$14, EBW_B.P$15, EBW_B.P$16, EBW_B.P$17, EBW_B.P$33, EBW_B.P$34, EBW_B.P$35, F3.1, MH1.B5,5, MOUNT_10.16_A.P$3, MOUNT_10.16_A.P$4, SJ3.2, TP10.TP
SOURCE-POS-A_T: C2.2, C3.1, D3.C, F3.2, R1.2, SHUNTMON-A.1 (RSP)
SOURCE-POS-B: EBW_A.P$1, EBW_A.P$3, EBW_A.P$4, EBW_A.P$5, EBW_A.P$6, EBW_A.P$7, EBW_A.P$8, EBW_A.P$9, EBW_A.P$10, EBW_A.P$11, EBW_A.P$12, EBW_A.P$13, EBW_A.P$14, EBW_A.P$15, EBW_A.P$16, EBW_A.P$17, EBW_A.P$33, EBW_A.P$34, EBW_A.P$35, F5.1, MH3.B5,5, MOUNT_10.16_B.P$3, MOUNT_10.16_B.P$4, SJ7.1, TP8.TP
SOURCE-POS-B_T: C5.2, C6.1, D5.C, F5.2, R3.2, SHUNTMON-B.1 (RSP)
UNI_REF: C14.1, MCP3208.6 (CH5), R7.1, R8.2, R26.1, R27.2, REF_SEL_A.1, REF_SEL_B.1
VBAT: 3.3V_BAT.2, CR1220.P+ (P$+), PCF8523.3 (VBAT)
VDD_PCF: C33T.1 (+), PCF8523.8 (VDD), R22.1
VDD_RTC_POSTJUMPER: R20.1, R21.1, R22.2, SJ2.2
VSENSE_A: R1.1, R2.2, SJ8.1
VSENSE_A_BUFFED: C10.1, LM258.1 (OUT), LM258.2 (-IN), MCP3208.2 (CH1)
VSENSE_A_TP: C21.1, LM258.3 (+IN), SJ8.2, U$1.P$1
VSENSE_B: R3.1, R4.2, SJ9.1
VSENSE_B_BUFFED: C12.1, LM258.6 (-IN), LM258.7 (OUT), MCP3208.4 (CH3)
VSENSE_B_TP: C20.1, LM258.5 (+IN), SJ9.2, U$4.P$1
V_IN_POSTFUSE: D1.C, F1.P$3 (2), F1.P$4 (2), TP4.TP
V_IN_PREFUSE: F1.P$1 (1), F1.P$2 (1), PWR.2
_RESET: GPIO_1.8

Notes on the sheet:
emonDC v3.6 use of ESP module inspired by Heatpumpmonitor project.
designed by Daniel Bates November 2018
Power Supply
Design is provided "AS IS" and "WITH ALL FAULTS. OpenEnergyMonitor DISCLAIMS ALL OTHER WARRANTIES, EXPRESS OR IMPLIED,
Hardware design files are licensed under the Creative Commons Attribution-ShareAlike 3.0 Unported License
DC INPUT & REGULATORS
Shunt Monitor B
Shunt Monitor A
ESP-12E/S/F
MICRO SD CARD
RFM69Pi Module Interface RFM69CW
MCP3208
PCF8523
Credit: Bob Lemaire. IoTaWatt v4.4 https://github.com/boblemaire/IoTaWatt/
SPI LCD DISPLAY
TEMPERATURE SENSOR
50mV MIN output desirable
REF VOLTAGE

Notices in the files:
parts and their libraries:
inductor-bourns: Copyright (C) 2008, Bob Starr
SparkFun-Connectors: Licensing: CC v3.0 Share-Alike You are welcome to use this library for commercial purposes.
SparkFun-Connectors: Licensing: Creative Commons ShareAlike 4.0 International - https://creativecommons.org/licenses/by-sa/4.0
